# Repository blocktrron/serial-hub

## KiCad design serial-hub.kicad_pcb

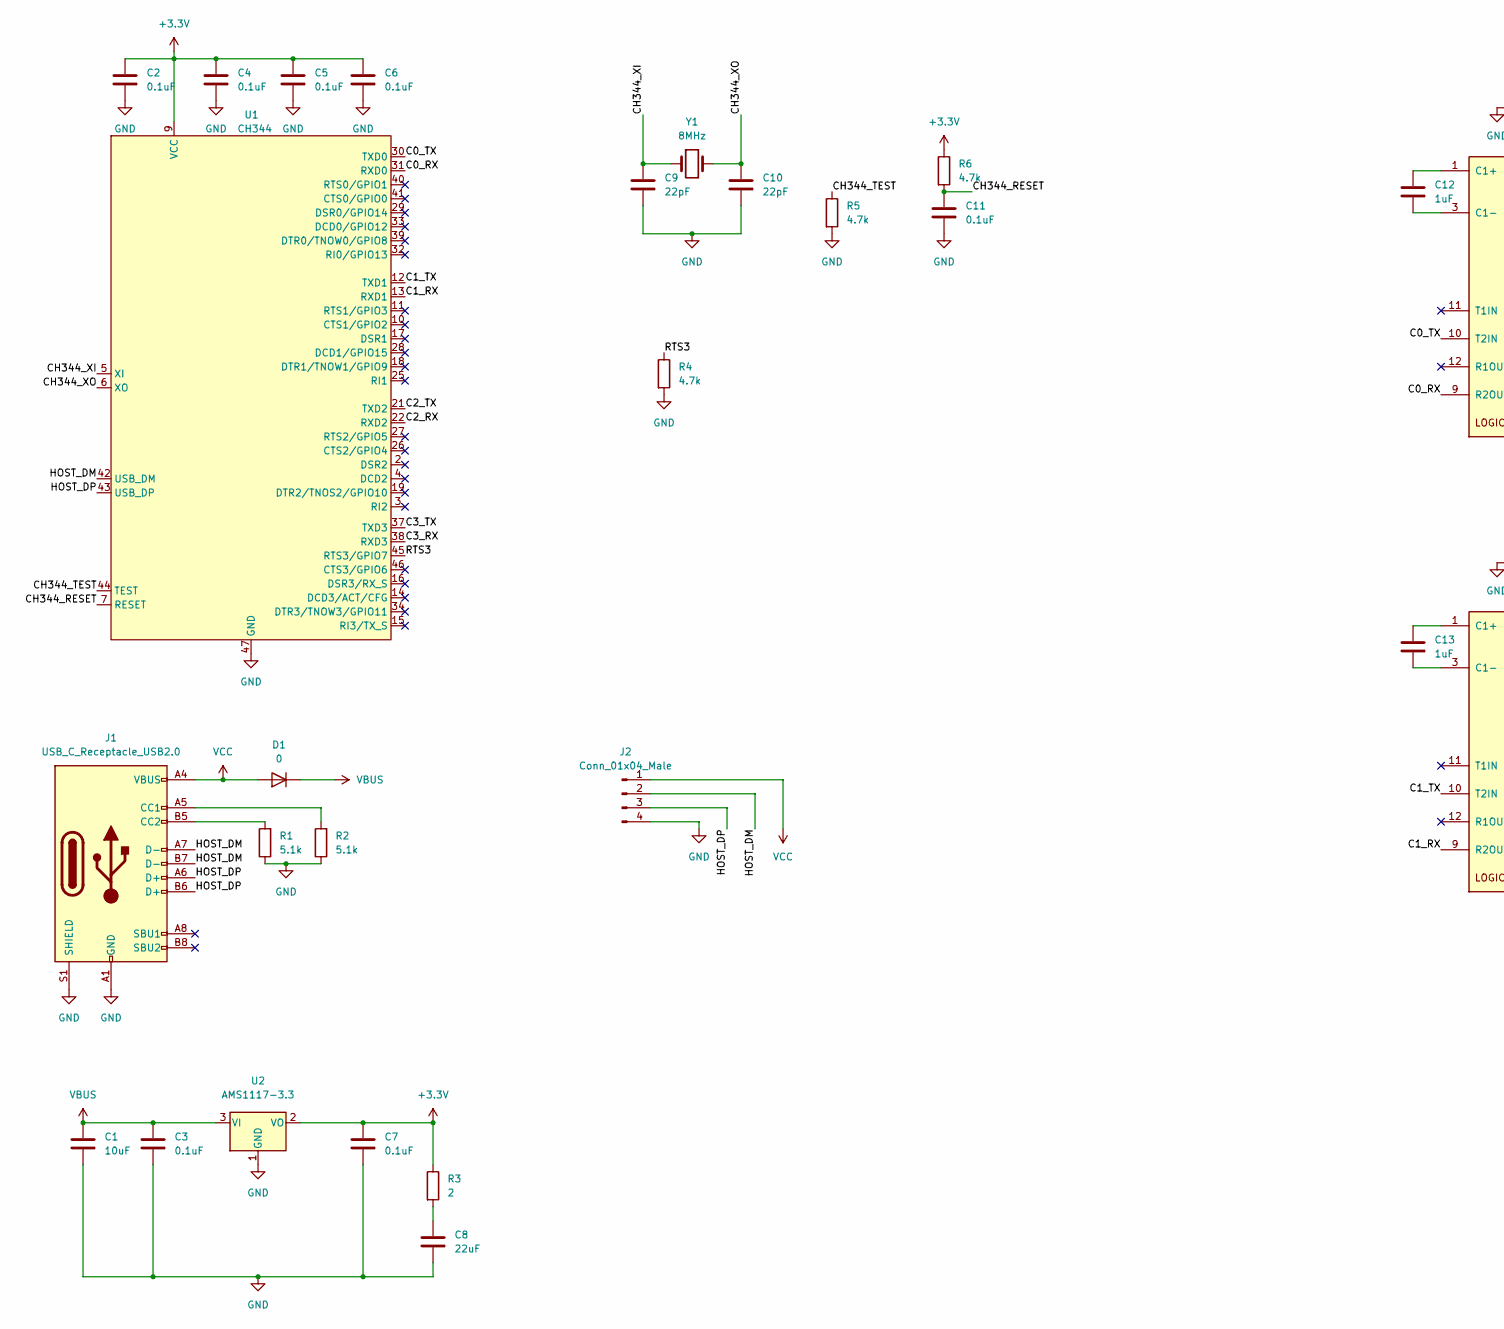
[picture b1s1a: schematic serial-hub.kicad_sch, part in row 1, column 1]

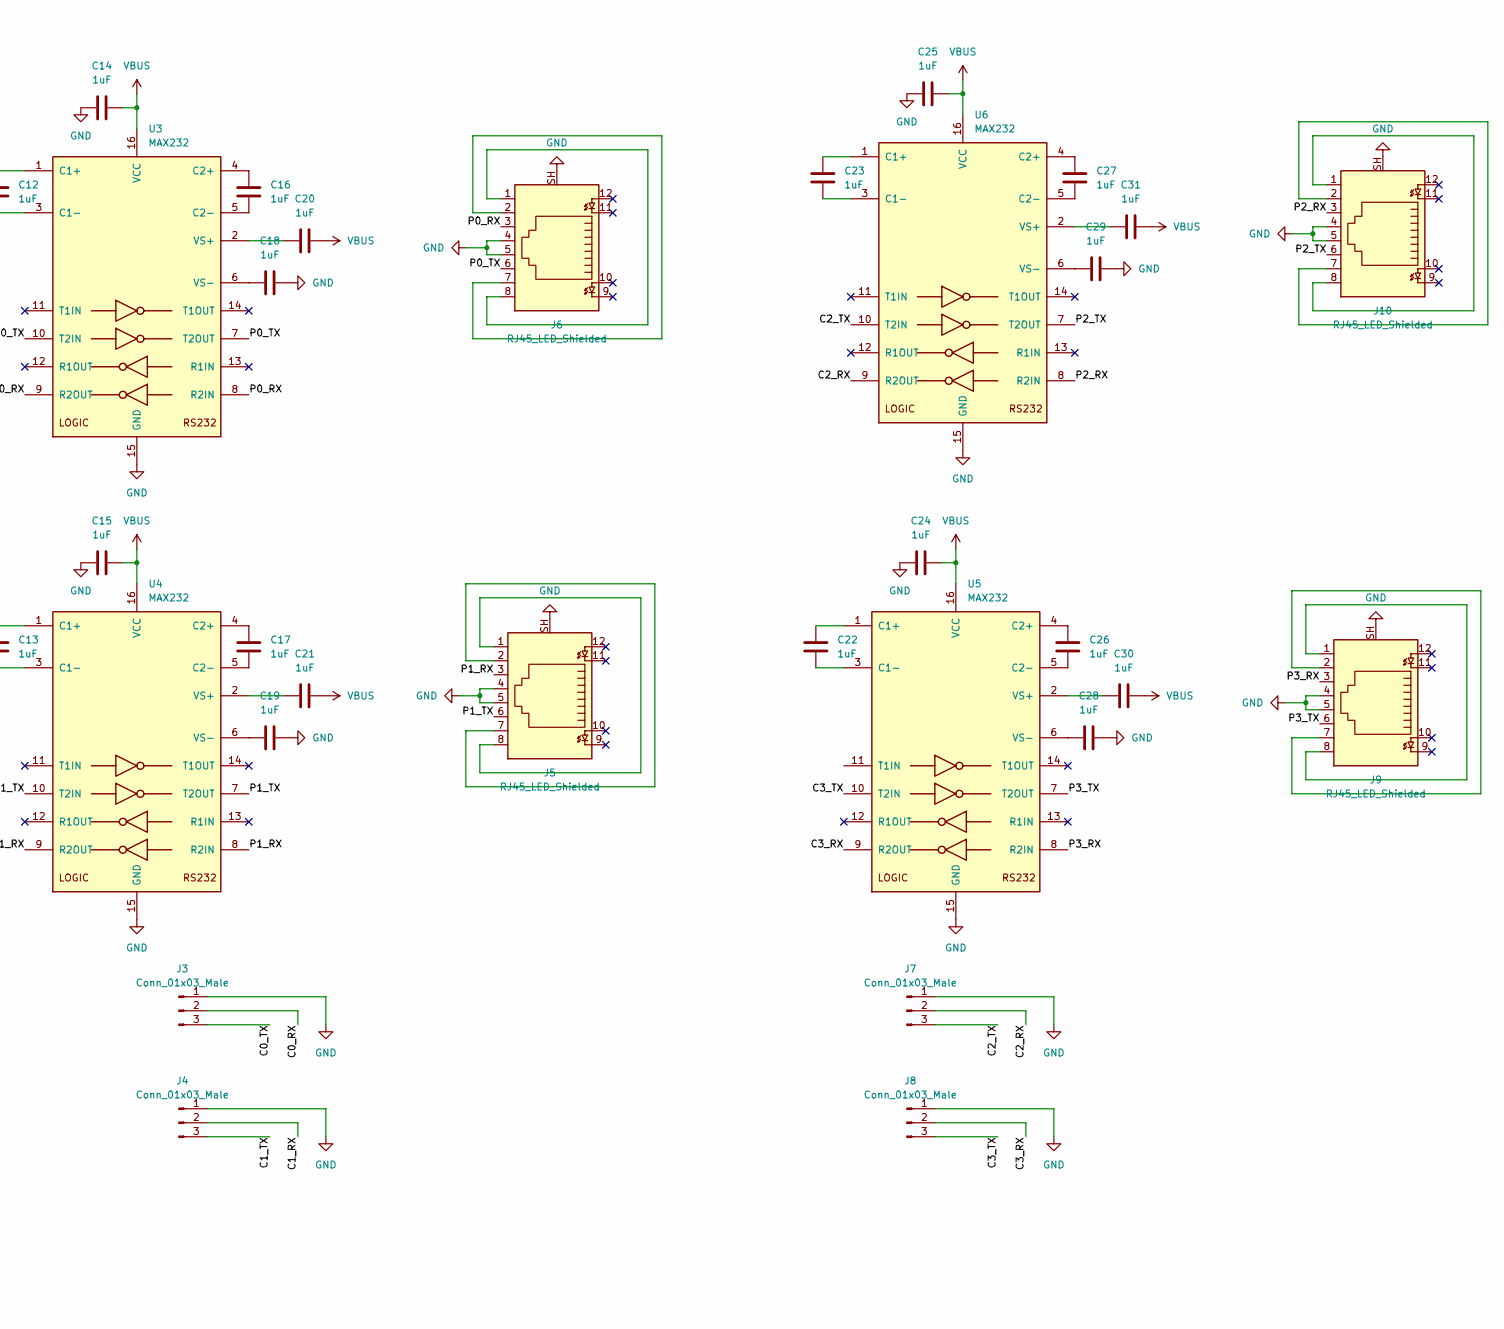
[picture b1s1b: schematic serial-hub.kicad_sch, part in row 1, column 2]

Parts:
C1: 10uF; C_0603_1608Metric; LCSC C96446
C2, C3, C4, C5, C6, C7, C11: 0.1uF; C_0603_1608Metric; LCSC C14663
C8: 22uF; C_0805_2012Metric; LCSC C45783
C9, C10: 22pF; C_0402_1005Metric; LCSC C1555
C12, C13, C14, C15, C16, C17, C18, C19, C20, C21, C22, C23, C24, C25, C26, C27, C28, C29, C30, C31: 1uF; C_0603_1608Metric; LCSC C15849
D1: 0; D_SOD-123; LCSC C8598
J1: USB_C_Receptacle_USB2.0; USB_C_Receptacle_XKB_U262-16XN-4BVC11; LCSC C2988369
J2: Conn_01x04_Male; PinHeader_1x04_P2.54mm_Vertical
J3, J4, J7, J8: Conn_01x03_Male; PinHeader_1x03_P2.54mm_Vertical
J5, J6, J9, J10: RJ45_LED_Shielded; RJ45_Amphenol_54602-x08_Horizontal; LCSC C2847314
R1, R2: 5.1k; R_0402_1005Metric; LCSC C25905
R3: 2; R_0603_1608Metric; LCSC C22977
R4, R5, R6: 4.7k; R_0402_1005Metric; LCSC C25900
U1: CH344; LQFP-48_7x7mm_P0.5mm; LCSC C2988084
U2: AMS1117-3.3; SOT-223-3_TabPin2; LCSC C6186
U3, U4, U5, U6: MAX232; SOIC-16_3.9x9.9mm_P1.27mm; LCSC C26860
Y1: 8MHz; Crystal_SMD_5032-2Pin_5.0x3.2mm; LCSC C115962

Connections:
+3.3V: C2.1, C4.1, C5.1, C6.1, C7.1, R3.1, R6.1, U1.9 (VCC), U1.24 (VCC), U1.36 (VCC), U1.48 (VCC), U2.2 (VO)
/C0_RX: J3.2, U1.31 (RXD0), U3.9 (R2OUT)
/C0_TX: J3.3, U1.30 (TXD0), U3.10 (T2IN)
/C1_RX: J4.2, U1.13 (RXD1), U4.9 (R2OUT)
/C1_TX: J4.3, U1.12 (TXD1), U4.10 (T2IN)
/C2_RX: J7.2, U1.22 (RXD2), U6.9 (R2OUT)
/C2_TX: J7.3, U1.21 (TXD2), U6.10 (T2IN)
/C3_RX: J8.2, U1.38 (RXD3), U5.9 (R2OUT)
/C3_TX: J8.3, U1.37 (TXD3), U5.10 (T2IN)
/CH344_RESET: C11.1, R6.2, U1.7 (RESET)
/CH344_TEST: R5.1, U1.44 (TEST)
/CH344_XI: C9.1, U1.5 (XI), Y1.1
/CH344_XO: C10.1, U1.6 (XO), Y1.2
/HOST_DM: J1.A7 (D-), J1.B7 (D-), J2.2, U1.42 (USB_DM)
/HOST_DP: J1.A6 (D+), J1.B6 (D+), J2.3, U1.43 (USB_DP)
/P0_RX: J6.3, U3.8 (R2IN)
/P0_TX: J6.6, U3.7 (T2OUT)
/P1_RX: J5.3, U4.8 (R2IN)
/P1_TX: J5.6, U4.7 (T2OUT)
/P2_RX: J10.3, U6.8 (R2IN)
/P2_TX: J10.6, U6.7 (T2OUT)
/P3_RX: J9.3, U5.8 (R2IN)
/P3_TX: J9.6, U5.7 (T2OUT)
/RTS3: R4.1, U1.45 (RTS3/GPIO7)
GND: C1.2, C2.2, C3.2, C4.2, C5.2, C6.2, C7.2, C8.2, C9.2, C10.2, C11.2, C14.1, C15.1, C18.2, C19.2, C24.1, C25.1, C28.2, C29.2, J1.A1 (GND), J1.A12 (GND), J1.B1 (GND), J1.B12 (GND), J1.S1 (SHIELD), J2.4, J3.1, J4.1, J5.4, J5.5, J5.SH, J6.4, J6.5, J6.SH, J7.1, J8.1, J9.4, J9.5, J9.SH, J10.4, J10.5, J10.SH, R1.1, R2.1, R4.2, R5.2, U1.8 (GND), U1.20 (GND), U1.23 (GND), U1.35 (GND), U1.47 (GND), U2.1 (GND), U3.15 (GND), U4.15 (GND), U5.15 (GND), U6.15 (GND)
unnamed: C8.1, R3.2
unnamed: C12.1, U3.1 (C1+)
unnamed: C12.2, U3.3 (C1-)
unnamed: C13.1, U4.1 (C1+)
unnamed: C13.2, U4.3 (C1-)
unnamed: C16.1, U3.4 (C2+)
unnamed: C16.2, U3.5 (C2-)
unnamed: C17.1, U4.4 (C2+)
unnamed: C17.2, U4.5 (C2-)
unnamed: C18.1, U3.6 (VS-)
unnamed: C19.1, U4.6 (VS-)
unnamed: C20.1, U3.2 (VS+)
unnamed: C21.1, U4.2 (VS+)
unnamed: C22.1, U5.1 (C1+)
unnamed: C22.2, U5.3 (C1-)
unnamed: C23.1, U6.1 (C1+)
unnamed: C23.2, U6.3 (C1-)
unnamed: C26.1, U5.4 (C2+)
unnamed: C26.2, U5.5 (C2-)
unnamed: C27.1, U6.4 (C2+)
unnamed: C27.2, U6.5 (C2-)
unnamed: C28.1, U5.6 (VS-)
unnamed: C29.1, U6.6 (VS-)
unnamed: C30.1, U5.2 (VS+)
unnamed: C31.1, U6.2 (VS+)
unnamed: J1.A5 (CC1), R2.2
unnamed: J1.B5 (CC2), R1.2
unnamed: J5.1, J5.8
unnamed: J5.2, J5.7
unnamed: J6.1, J6.8
unnamed: J6.2, J6.7
unnamed: J9.1, J9.8
unnamed: J9.2, J9.7
unnamed: J10.1, J10.8
unnamed: J10.2, J10.7
VBUS: C1.1, C3.1, C14.2, C15.2, C20.2, C21.2, C24.2, C25.2, C30.2, C31.2, D1.1 (K), U2.3 (VI), U3.16 (VCC), U4.16 (VCC), U5.16 (VCC), U6.16 (VCC)
VCC: D1.2 (A), J1.A4 (VBUS), J1.A9 (VBUS), J1.B4 (VBUS), J1.B9 (VBUS), J2.1

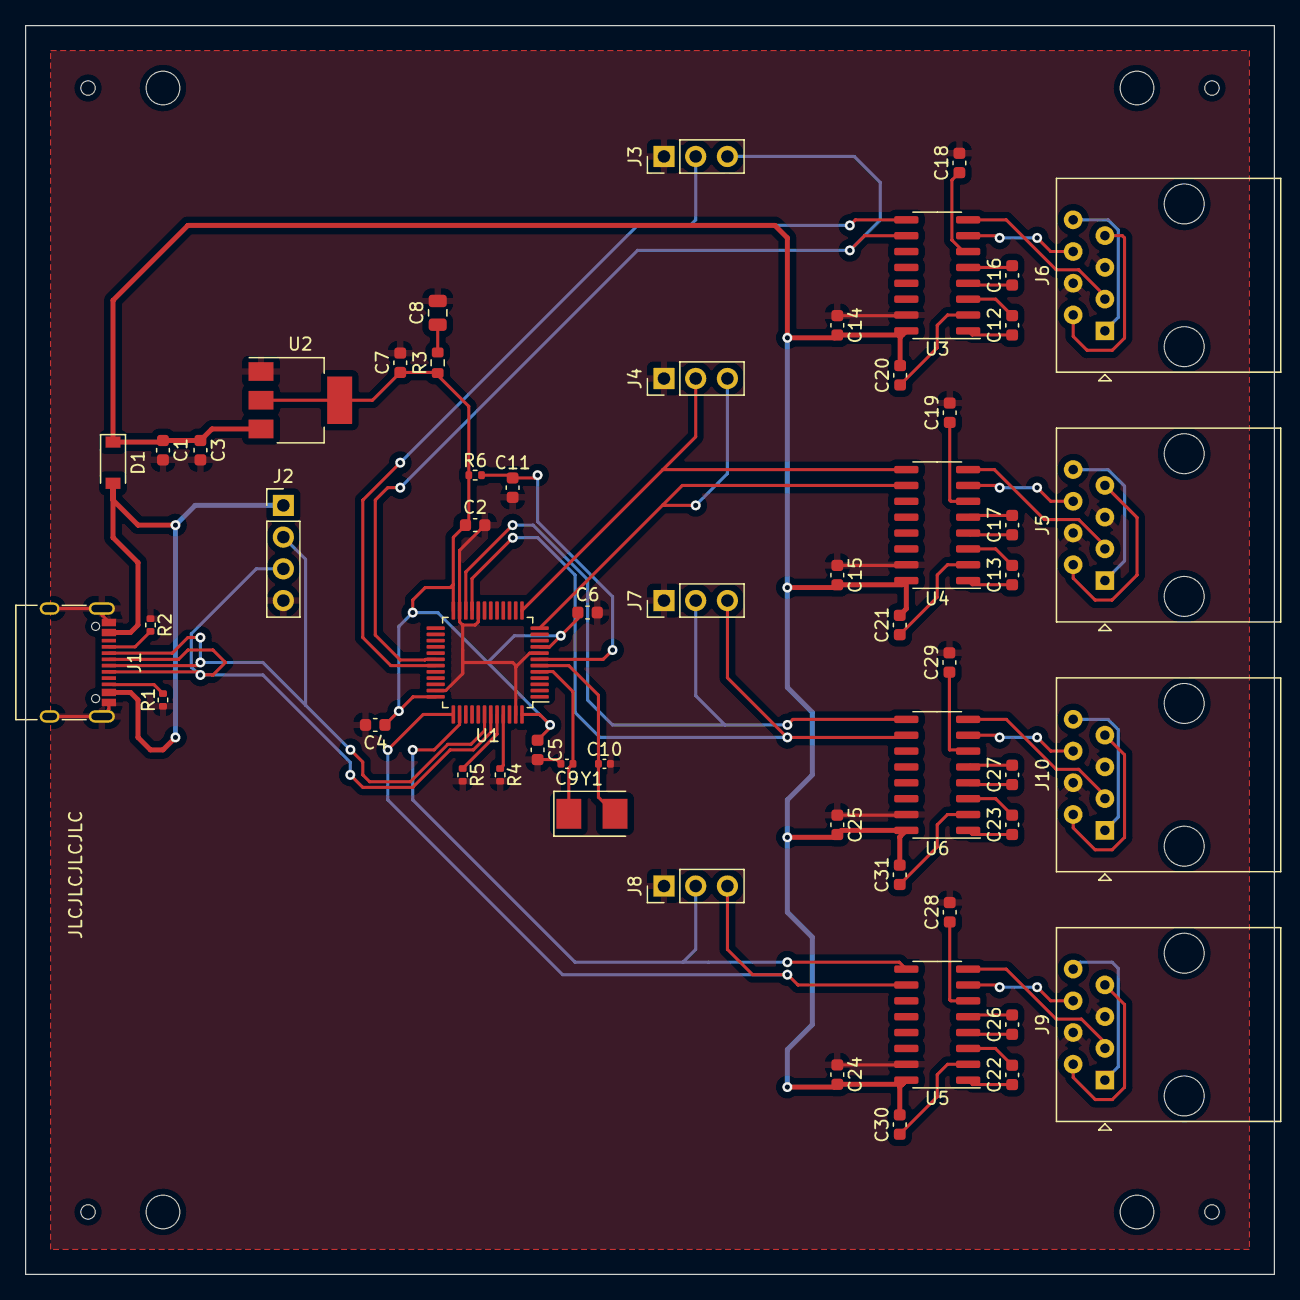
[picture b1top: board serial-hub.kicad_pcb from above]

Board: 2 copper layers, 100.0 x 100.0 mm, 55 parts (0 on the bottom side), 62 nets.

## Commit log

2023-04-21 initial wip
2023-04-23 update gitignore
2023-04-23 init pcb design
2023-04-23 fix max232 caps
2023-04-23 update schematic
2023-04-23 update sch
2023-04-23 update PCB
2023-04-23 fix USB-C part number
2023-04-23 add LCSC ids to pcb
2023-04-23 add test-pins for UART
2023-04-23 switch USB-C / add CH344 input caps
2023-04-24 add mounting holes
2023-04-24 lock mounting holes
2023-05-10 export
2023-05-10 gitignore: add old schematic
2023-05-10 schematic: fix incorrect JLC part assignment
2023-05-25 board: fix wrong RJ45 pins
